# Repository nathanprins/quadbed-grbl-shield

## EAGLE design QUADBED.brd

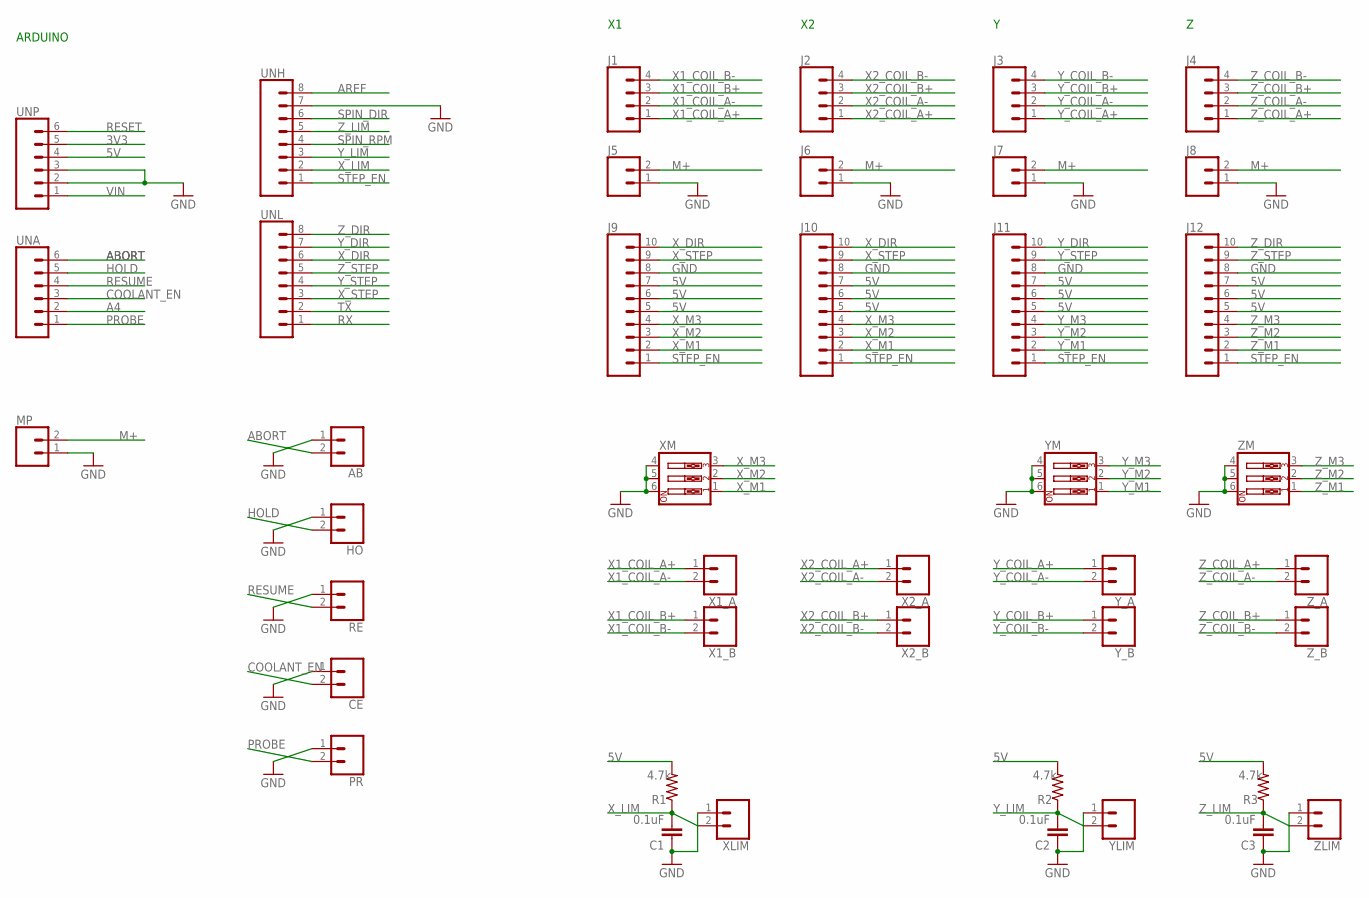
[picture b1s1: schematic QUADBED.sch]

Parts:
AB: CONN_023.5MM; SCREWTERMINAL-3.5MM-2
C1, C2, C3: 0.1uF; 0603
CE: CONN_023.5MM; SCREWTERMINAL-3.5MM-2
HO: CONN_023.5MM; SCREWTERMINAL-3.5MM-2
J1, J2, J3, J4: CONN_04; 1X04
J5, J6, J7, J8: CONN_02; 1X02
J9, J10, J11, J12: CONN_10"; 1X10
MP: CONN_023.5MM; SCREWTERMINAL-3.5MM-2
PR: CONN_023.5MM; SCREWTERMINAL-3.5MM-2
R1, R2, R3: 4.7k; 0603
RE: CONN_023.5MM; SCREWTERMINAL-3.5MM-2
UNA: CONN_06SILK_FEMALE_PTH; 1X06
UNH: CONN_08"; 1X08
UNL: CONN_08"; 1X08
UNP: CONN_06SILK_FEMALE_PTH; 1X06
X1_A, X1_B, X2_A, X2_B: CONN_023.5MM; SCREWTERMINAL-3.5MM-2
XLIM: CONN_023.5MM; SCREWTERMINAL-3.5MM-2
XM: SW_DIP-3; EDG-03
YLIM: CONN_023.5MM; SCREWTERMINAL-3.5MM-2
YM: SW_DIP-3; EDG-03
Y_A: CONN_023.5MM; SCREWTERMINAL-3.5MM-2
Y_B: CONN_023.5MM; SCREWTERMINAL-3.5MM-2
ZLIM: CONN_023.5MM; SCREWTERMINAL-3.5MM-2
ZM: SW_DIP-3; EDG-03
Z_A: CONN_023.5MM; SCREWTERMINAL-3.5MM-2
Z_B: CONN_023.5MM; SCREWTERMINAL-3.5MM-2

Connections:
3V3: UNP.5
5V: J9.5, J9.6, J9.7, J10.5, J10.6, J10.7, J11.5, J11.6, J11.7, J12.5, J12.6, J12.7, R1.2, R2.2, R3.2, UNP.4
A4: UNA.2
ABORT: AB.2, UNA.6
AREF: UNH.8
COOLANT_EN: CE.2, UNA.3
GND: AB.1, C1.1, C2.1, C3.1, CE.1, HO.1, J5.1, J6.1, J7.1, J8.1, J9.8, J10.8, J11.8, J12.8, MP.1, PR.1, RE.1, UNH.7, UNP.2, UNP.3, XLIM.1, XM.4, XM.5, XM.6, YLIM.1, YM.4, YM.5, YM.6, ZLIM.1, ZM.4, ZM.5, ZM.6
HOLD: HO.2, UNA.5
M+: J5.2, J6.2, J7.2, J8.2, MP.2
PROBE: PR.2, UNA.1
RESET: UNP.6
RESUME: RE.2, UNA.4
RX: UNL.1
SPIN_DIR: UNH.6
SPIN_RPM: UNH.4
STEP_EN: J9.1, J10.1, J11.1, J12.1, UNH.1
TX: UNL.2
VIN: UNP.1
X1_COIL_A+: J1.1, X1_A.1
X1_COIL_A-: J1.2, X1_A.2
X1_COIL_B+: J1.3, X1_B.1
X1_COIL_B-: J1.4, X1_B.2
X2_COIL_A+: J2.1, X2_A.1
X2_COIL_A-: J2.2, X2_A.2
X2_COIL_B+: J2.3, X2_B.1
X2_COIL_B-: J2.4, X2_B.2
X_DIR: J9.10, J10.10, UNL.6
X_LIM: C1.2, R1.1, UNH.2, XLIM.2
X_M1: J9.2, J10.2, XM.1
X_M2: J9.3, J10.3, XM.2
X_M3: J9.4, J10.4, XM.3
X_STEP: J9.9, J10.9, UNL.3
Y_COIL_A+: J3.1, Y_A.1
Y_COIL_A-: J3.2, Y_A.2
Y_COIL_B+: J3.3, Y_B.1
Y_COIL_B-: J3.4, Y_B.2
Y_DIR: J11.10, UNL.7
Y_LIM: C2.2, R2.1, UNH.3, YLIM.2
Y_M1: J11.2, YM.1
Y_M2: J11.3, YM.2
Y_M3: J11.4, YM.3
Y_STEP: J11.9, UNL.4
Z_COIL_A+: J4.1, Z_A.1
Z_COIL_A-: J4.2, Z_A.2
Z_COIL_B+: J4.3, Z_B.1
Z_COIL_B-: J4.4, Z_B.2
Z_DIR: J12.10, UNL.8
Z_LIM: C3.2, R3.1, UNH.5, ZLIM.2
Z_M1: J12.2, ZM.1
Z_M2: J12.3, ZM.2
Z_M3: J12.4, ZM.3
Z_STEP: J12.9, UNL.5

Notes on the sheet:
ARDUINO

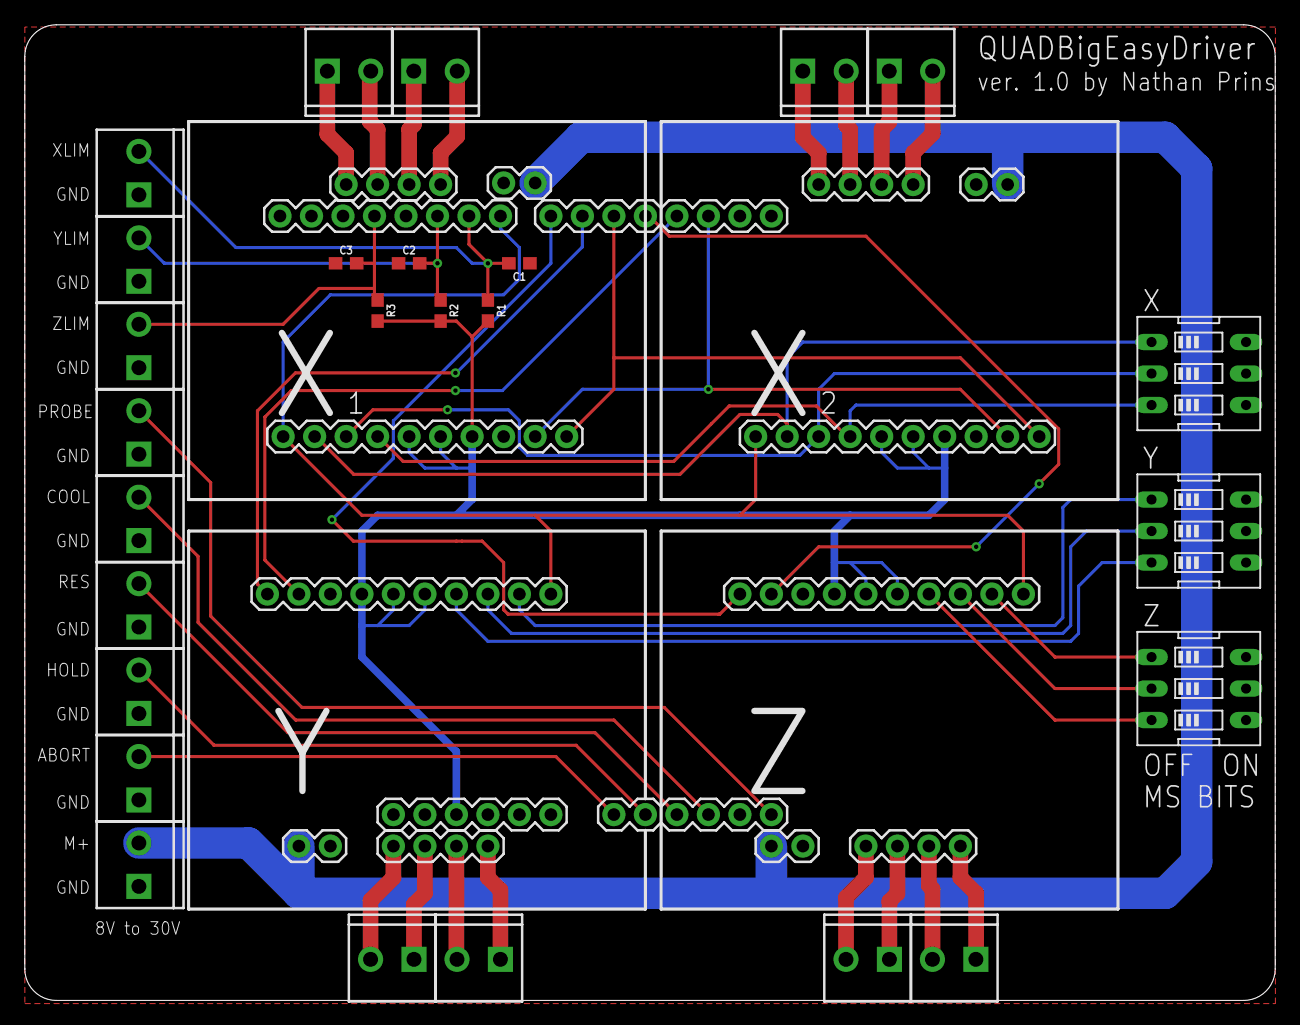
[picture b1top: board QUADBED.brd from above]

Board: 2 copper layers, 100.8 x 78.7 mm, 42 parts (0 on the bottom side), 43 nets.

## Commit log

2019-07-07 ver. 1.0

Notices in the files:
parts and their libraries:
SparkFun-Capacitors: Licensing: Creative Commons ShareAlike 4.0 International - https://creativecommons.org/licenses/by-sa/4.0
